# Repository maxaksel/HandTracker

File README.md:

# HandTracker

Project members: Max Bowman and Josh Stidham

This repository contains Eagle hardware files and C software files for
our final project.

Simulink navigation equation blocks used for visualization courtesy of Christopher Lum (University of Washington).

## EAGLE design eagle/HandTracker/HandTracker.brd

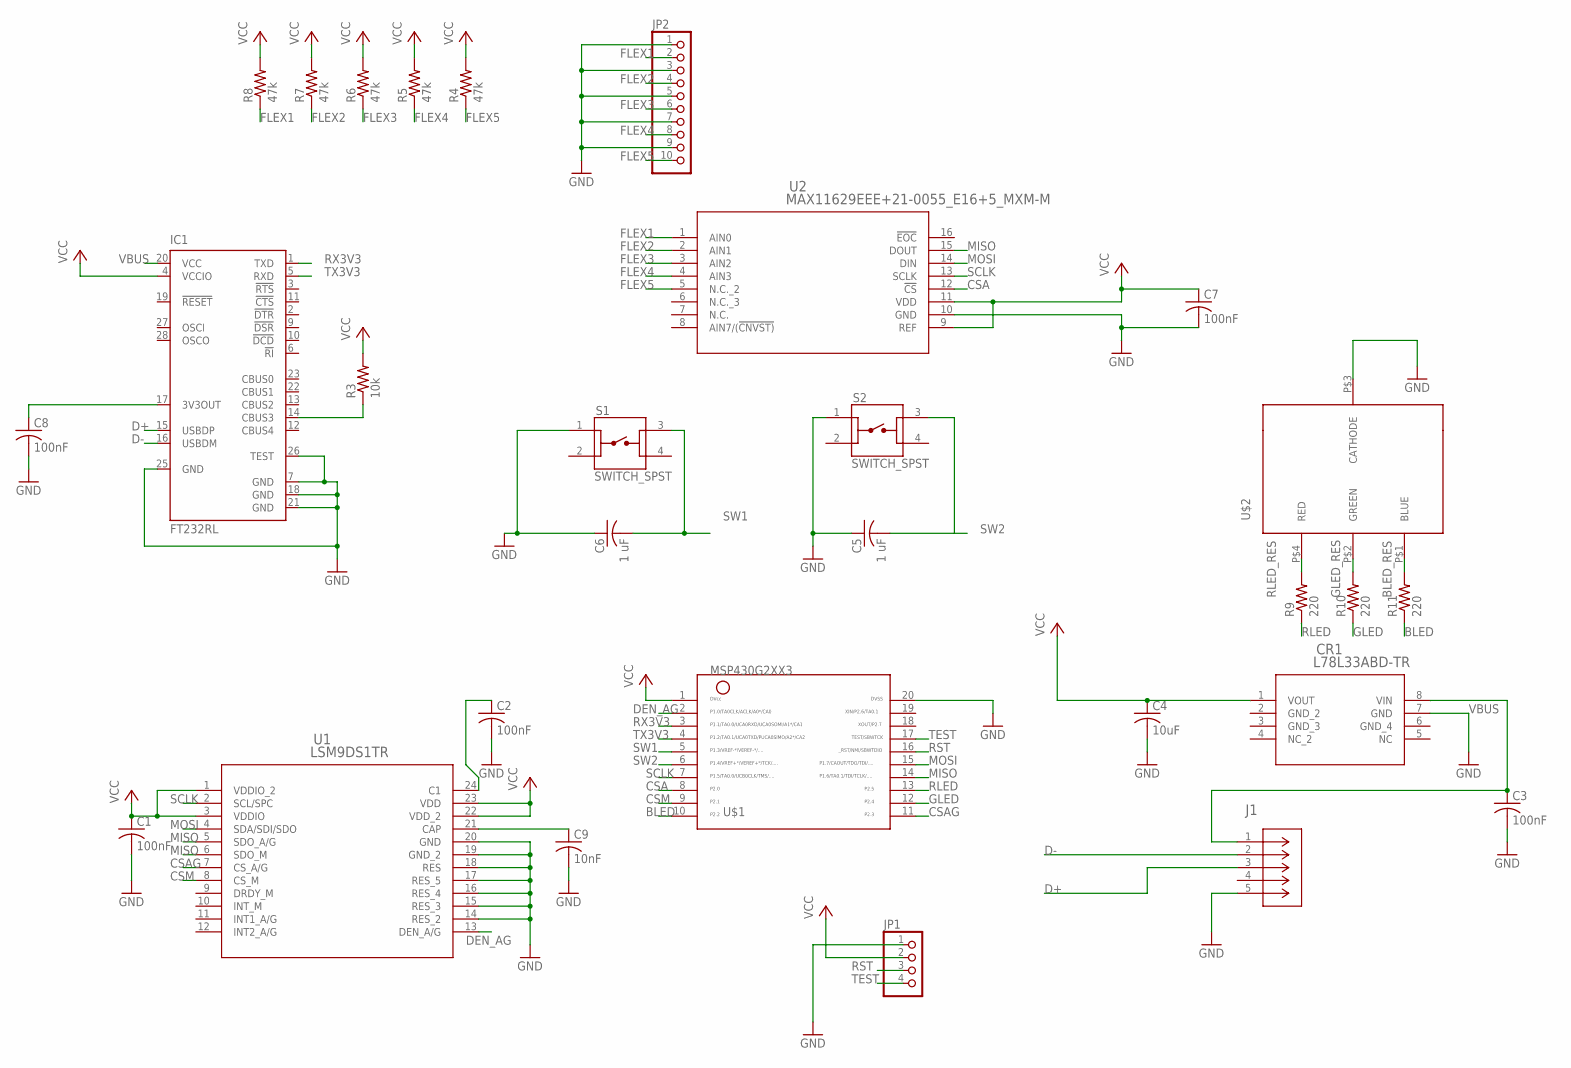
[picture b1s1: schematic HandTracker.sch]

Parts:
C1, C2, C3, C7, C8: 100nF; C1206
C4: 10uF; C1206
C5, C6: 1 uF; C1206
C9: 10nF; C1206
CR1: L78L33ABD-TR; SO-8_STM
IC1: FT232RL; SSOP28
J1: ZX62-AB-5PA(31); CONN5_ZX62-AB-5PA_HIR
JP1: PINHD-1X4/90; 1X04/90
JP2: PINHD-1X10; 1X10
R3: 10k; R1206
R4, R5, R6, R7, R8: 47k; R1206
R9, R10, R11: 220; R1206
S1, S2: SWITCH_SPST; SW_1825910-7
U1: LSM9DS1TR; LGA-24_3X3P5X1_STM
U2: MAX11629EEE+21-0055_E16+5_MXM-M; 21-0055_E16+5_MXM-M
U$1: MSP430G2XX3TSSOP; PW20
U$2: NTE30158

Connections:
BLED: R11.1, U$1.10
BLED_RES: R11.2, U$2.P$1 (BLUE); also elsewhere on the board
CSA: U2.12 (!CS), U$1.8
CSAG: U1.7 (CS_A/G), U$1.11
CSM: U1.8 (CS_M), U$1.9
D+: IC1.15 (USBDP), J1.3 (D+)
D-: IC1.16 (USBDM), J1.2 (D-)
DEN_AG: U1.13 (DEN_A/G), U$1.2
FLEX1: JP2.2, R8.1, U2.1 (AIN0)
FLEX2: JP2.4, R7.1, U2.2 (AIN1)
FLEX3: JP2.6, R6.1, U2.3 (AIN2)
FLEX4: JP2.8, R5.1, U2.4 (AIN3)
FLEX5: JP2.10, R4.1, U2.5 (N.C._2)
GLED: R10.1, U$1.12
GLED_RES: R10.2, U$2.P$2 (GREEN); also elsewhere on the board
GND: C1.2, C2.2, C3.2, C4.2, C5.1, C6.1, C7.2, C8.2, C9.2, CR1.7 (GND), IC1.7 (GND), IC1.18 (GND), IC1.21 (GND), IC1.25 (GND), IC1.26 (TEST), J1.5 (GND), JP1.1, JP2.1, JP2.3, JP2.5, JP2.7, JP2.9, S1.1, S2.1, U1.14 (RES_2), U1.15 (RES_3), U1.16 (RES_4), U1.17 (RES_5), U1.18 (RES), U1.19 (GND_2), U1.20 (GND), U2.10 (GND), U$1.20, U$2.P$3 (CATHODE); also elsewhere on the board
MISO: U1.5 (SDO_A/G), U1.6 (SDO_M), U2.15 (DOUT), U$1.14
MOSI: U1.4 (SDA/SDI/SDO), U2.14 (DIN), U$1.15
unnamed: C2.1, U1.24 (C1)
unnamed: C8.1, IC1.17 (3V3OUT)
unnamed: IC1.14 (CBUS3), R3.1
unnamed: C9.1, U1.21 (CAP)
RLED: R9.1, U$1.13
RLED_RES: R9.2, U$2.P$4 (RED); also elsewhere on the board
RST: JP1.3, U$1.16
RX3V3: IC1.1 (TXD), U$1.3
SCLK: U1.2 (SCL/SPC), U2.13 (SCLK), U$1.7
SW1: C6.2, S1.3, U$1.5
SW2: C5.2, S2.3, U$1.6
TEST: JP1.4, U$1.17
TX3V3: IC1.5 (RXD), U$1.4
VBUS: C3.1, CR1.8 (VIN), IC1.20 (VCC), J1.1 (VCC)
VCC: C1.1, C4.1, C7.1, CR1.1 (VOUT), IC1.4 (VCCIO), JP1.2, R3.2, R4.2, R5.2, R6.2, R7.2, R8.2, U1.1 (VDDIO_2), U1.3 (VDDIO), U1.22 (VDD_2), U1.23 (VDD), U2.9 (REF), U2.11 (VDD), U$1.1

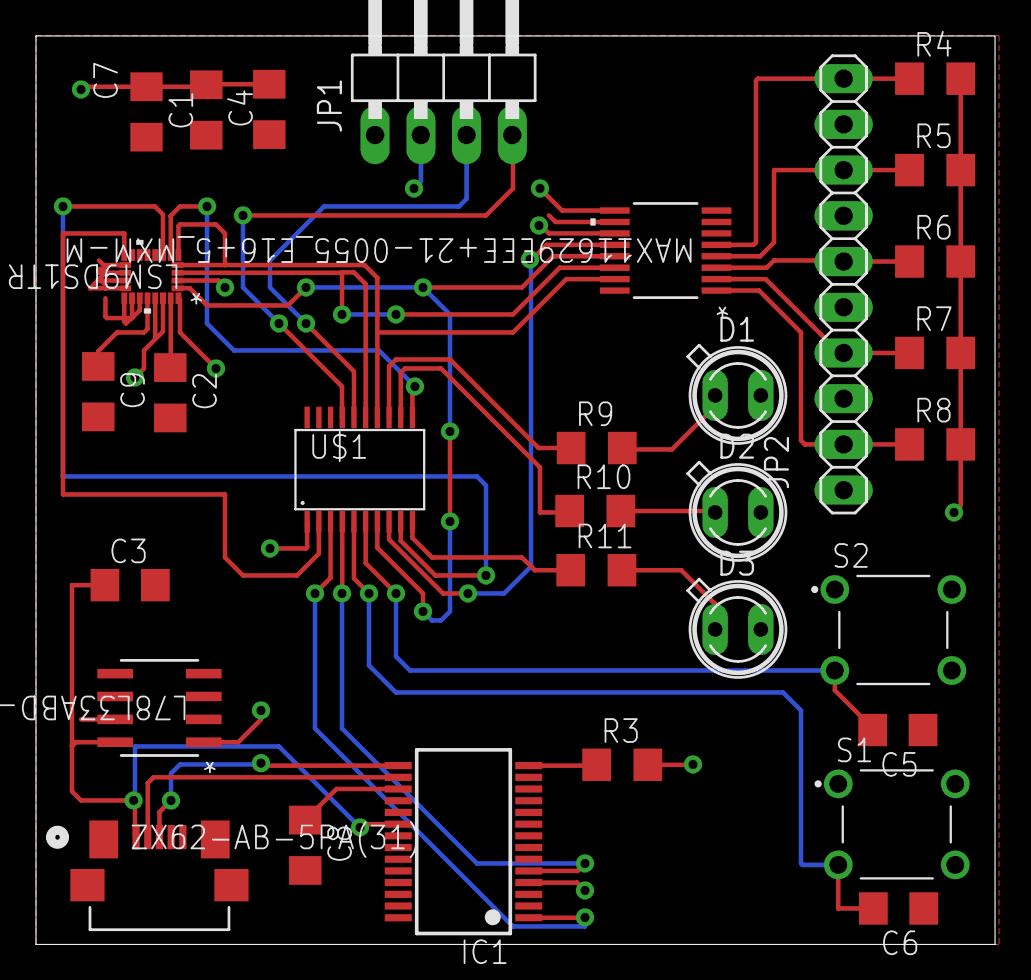
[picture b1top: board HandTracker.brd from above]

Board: 2 copper layers, 53.3 x 50.5 mm, 31 parts (0 on the bottom side), 33 nets.

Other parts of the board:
D1, D2, D3: SFH482

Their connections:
BLED_RES: D3.A; also elsewhere on the board
GLED_RES: D2.A; also elsewhere on the board
GND: D1.K, D2.K, D3.K; also elsewhere on the board
RLED_RES: D1.A; also elsewhere on the board

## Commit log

2022-03-30 Initial commit.
2022-03-30 Add project structure.
2022-04-04 Added Project Structure
2022-04-04 Started Adding Components to Schematic
2022-04-07 Started Populating Schematic with ICs
2022-04-07 Continued Populating Schematic and began making connections
2022-04-07 continued making connections
2022-04-07 completed connections for all components except FT232
2022-04-07 added FT232RL, still need to add LED
2022-04-08 added led, completed schematic
2022-04-08 updated passive component values to reflect recommended operating conditions for various ICs
2022-04-08 removed USB termination resistors
2022-04-08 Changed linear voltage regulator.
2022-04-08 Add board file.
2022-04-09 Board routing minus VDD and GND planes.
2022-04-09 Draft 1 PCB with GND and VCC planes.
2022-04-10 Fix LED and route planes.
2022-04-10 replaced rgb led with three LEDs
2022-04-10 Routed LEDs and fixed clearance issues.
2022-04-10 Add machining files generated with CAM job.
2022-04-11 Button and LED IO software.
2022-04-11 Watchdog code.
2022-04-13 Timer A interrupt code.
2022-04-18 rough code with some basic SPI functions
2022-04-22 LSM9DS1 SPI code.
2022-04-22 MATLAB code.
2022-04-23 added files for SPI, SYSTEM (for later use), test (also for later use)
2022-04-24 updated spi API to be clearer, added uart files. Both untested
2022-04-24 Fixed + tested SPI async functions
2022-04-24 minor changes to UART API, need to make more significant changes to structure of Interrupt handlers
2022-04-24 added two spi functions to switc between ADC + LSM9DS1, tested with main
2022-04-25 created serial file with combined UART + SPI ISRs, tested UART with FTDI232 chip
2022-04-28 Clearer Comments
2022-04-28 UC0 RX Interrupt now declares SPI transmission to be complete if buffer is overrun
2022-04-28 Flight simulator and MATLAB read code. LSM9DS1 and resistor ADC code.
2022-04-29 began implementing main.c, modified timer code for use in this device (removed SW divider), changed SPI, UART baud rates, and modified button code for polling
2022-04-29 updated resistor function prototypes and continued system integration in main.c
2022-04-29 Software for debugging serial communications.
2022-04-29 lots of debugging
2022-04-29 Matlab sensor fusion update.
2022-04-29 added volatile keyword to global vars modified by interrupts
2022-04-29 Add sensor fusion algorithm. Add custom glove Simulink block.
2022-04-29 Modified code to read resistors in MATLAB from packet properly
2022-04-30 MATLAB IMU calibration code and flight sim code.
2022-04-30 packet Endianness matches Matlab Code's expectations
2022-04-30 reimplemented Kalman filter
2022-04-30 fixed timing, LEDs, and got Kalman filter working in MATLAB
2022-05-01 Add IMU calibration mats. Add magnetometer support. Simulink data block.
2022-05-01 Simulink AHRS model.
2022-05-02 Fixed Magnetometer
2022-05-02 fixed compiler warnings related to casting volitile to nonvolatile variable with cast
2022-05-02 Working MATLAB files.

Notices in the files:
parts and their libraries:
COPYRIGHT: Copyright (C) 2022 Ultra Librarian. All rights reserved.
